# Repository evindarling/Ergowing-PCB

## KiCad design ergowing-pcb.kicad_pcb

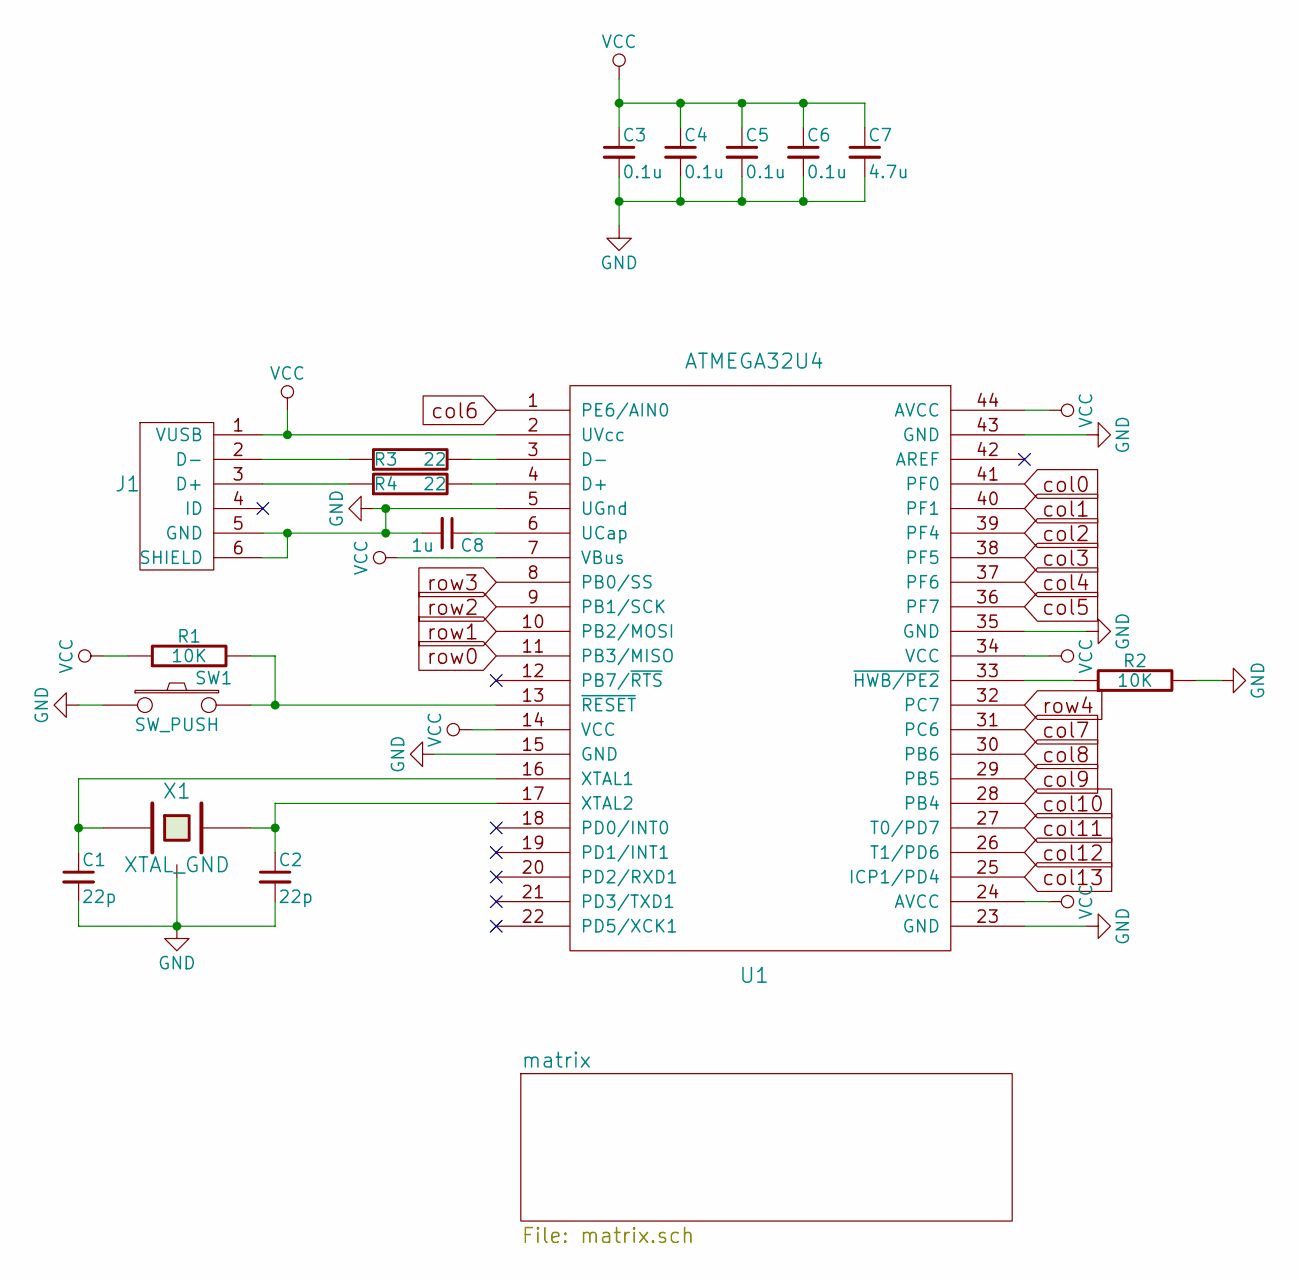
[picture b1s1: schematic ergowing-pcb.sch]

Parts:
C1, C2: 22p; C_0805_HandSoldering
C3, C4, C5, C6: 0.1u; C_0805_HandSoldering
C7: 4.7u; C_0805_HandSoldering
C8: 1u; C_0805_HandSoldering
J1: USB_mini_micro_B; USB_miniB_hirose_5S8
R1, R2: 10K; R_0805_HandSoldering
R3, R4: 22; R_0805_HandSoldering
SW1: SW_PUSH; SW_SPST_TL3342
U1: ATMEGA32U4; TQFP-44_10x10mm_Pitch0.8mm
X1: XTAL_GND; crystal_FA238-TSX3225

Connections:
GND: C1.2, C2.2, C3.2, C4.2, C5.2, C6.2, C7.2, C8.2, J1.5 (GND), J1.6 (SHIELD), R2.2, SW1.1, U1.5 (UGnd), U1.15 (GND), U1.23 (GND), U1.35 (GND), U1.43 (GND), X1.3; also elsewhere on the board
unnamed: C1.1, U1.16 (XTAL1), X1.1
unnamed: C2.1, U1.17 (XTAL2), X1.2
unnamed: C8.1, U1.6 (UCap)
unnamed: J1.2 (D-), R3.1
unnamed: J1.3 (D+), R4.1
unnamed: R1.2, SW1.2, U1.13 (~RESET)
unnamed: R2.1, U1.33 (~HWB/PE2)
unnamed: R3.2, U1.3 (D-)
unnamed: R4.2, U1.4 (D+)
VCC: C3.1, C4.1, C5.1, C6.1, C7.1, J1.1 (VUSB), R1.1, U1.2 (UVcc), U1.7 (VBus), U1.14 (VCC), U1.24 (AVCC), U1.34 (VCC), U1.44 (AVCC)
col0: U1.41 (PF0); also elsewhere on the board
col1: U1.40 (PF1); also elsewhere on the board
col2: U1.39 (PF4); also elsewhere on the board
col3: U1.38 (PF5); also elsewhere on the board
col4: U1.37 (PF6); also elsewhere on the board
col5: U1.36 (PF7); also elsewhere on the board
col6: U1.1 (PE6/AIN0); also elsewhere on the board
col7: U1.31 (PC6); also elsewhere on the board
col8: U1.30 (PB6); also elsewhere on the board
col9: U1.29 (PB5); also elsewhere on the board
col10: U1.28 (PB4); also elsewhere on the board
col11: U1.27 (T0/PD7); also elsewhere on the board
col12: U1.26 (T1/PD6); also elsewhere on the board
col13: U1.25 (ICP1/PD4); also elsewhere on the board
row0: U1.11 (PB3/MISO); also elsewhere on the board
row1: U1.10 (PB2/MOSI); also elsewhere on the board
row2: U1.9 (PB1/SCK); also elsewhere on the board
row3: U1.8 (PB0/SS); also elsewhere on the board
row4: U1.32 (PC7); also elsewhere on the board

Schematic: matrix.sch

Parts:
D0:0, D0:1, D0:2, D0:3, D0:4, D1:0, D1:1, D1:2, D1:3, D1:4, D2:0, D2:1, D2:2, D2:3, D2:4, D3:0, D3:1, D3:2, D3:3, D3:4, D4:0, D4:1, D4:2, D4:3, D4:4, D5:0, D5:1, D5:2, D5:3, D5:4, D6:0, D7:0, D7:4, D8:0, D8:1, D8:2, D8:3, D8:4, D9:0, D9:1, D9:2, D9:3, D9:4, D10:0, D10:1, D10:2, D10:3, D10:4, D11:0, D11:1, D11:2, D11:3, D11:4, D12:0, D12:1, D12:2, D12:3, D12:4, D13:0, D13:1, D13:2, D13:3, D13:4: D; D_SOD123_axial
D6:1, D6:3, D7:1, D7:3: D; Mx_Alps_150
K0:0, K0:1, K0:2, K0:3, K0:4: KEYSW; Mx_Alps_150_R-5deg
K1:0, K1:1, K1:2, K1:3, K1:4, K2:0, K2:1, K2:2, K2:3, K2:4, K3:0, K3:1, K3:2, K3:3, K3:4, K4:0, K4:1, K4:2, K4:3, K4:4, K5:0, K5:1, K5:2, K5:3, K6:0: KEYSW; Mx_Alps_100_R-5deg
K5:4: KEYSW; Mx_Alps_200
K6:1, K6:3, K7:1, K7:3: KEYSW; Mx_Alps_150
K7:0, K7:4, K8:0, K8:1, K8:2, K8:3, K8:4, K9:0, K9:1, K9:2, K9:3, K9:4, K10:0, K10:1, K10:2, K10:3, K10:4, K11:0, K11:1, K11:2, K11:3, K11:4, K12:0, K12:1, K12:2, K12:3, K12:4: KEYSW; Mx_Alps_100_R5deg
K13:0, K13:1, K13:2, K13:3, K13:4: KEYSW; Mx_Alps_150_R5deg

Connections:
unnamed: D0:0.2, K0:0.2
unnamed: D0:1.2, K0:1.2
unnamed: D0:2.2, K0:2.2
unnamed: D0:3.2, K0:3.2
unnamed: D0:4.2, K0:4.2
unnamed: D1:0.2, K1:0.2
unnamed: D1:1.2, K1:1.2
unnamed: D1:2.2, K1:2.2
unnamed: D1:3.2, K1:3.2
unnamed: D1:4.2, K1:4.2
unnamed: D2:0.2, K2:0.2
unnamed: D2:1.2, K2:1.2
unnamed: D2:2.2, K2:2.2
unnamed: D2:3.2, K2:3.2
unnamed: D2:4.2, K2:4.2
unnamed: D3:0.2, K3:0.2
unnamed: D3:1.2, K3:1.2
unnamed: D3:2.2, K3:2.2
unnamed: D3:3.2, K3:3.2
unnamed: D3:4.2, K3:4.2
unnamed: D4:0.2, K4:0.2
unnamed: D4:1.2, K4:1.2
unnamed: D4:2.2, K4:2.2
unnamed: D4:3.2, K4:3.2
unnamed: D4:4.2, K4:4.2
unnamed: D5:0.2, K5:0.2
unnamed: D5:1.2, K5:1.2
unnamed: D5:2.2, K5:2.2
unnamed: D5:3.2, K5:3.2
unnamed: D5:4.2, K5:4.2
unnamed: D6:0.2, K6:0.2
unnamed: D6:1.2, K6:1.2
unnamed: D6:3.2, K6:3.2
unnamed: D7:0.2, K7:0.2
unnamed: D7:1.2, K7:1.2
unnamed: D7:3.2, K7:3.2
unnamed: D7:4.2, K7:4.2
unnamed: D8:0.2, K8:0.2
unnamed: D8:1.2, K8:1.2
unnamed: D8:2.2, K8:2.2
unnamed: D8:3.2, K8:3.2
unnamed: D8:4.2, K8:4.2
unnamed: D9:0.2, K9:0.2
unnamed: D9:1.2, K9:1.2
unnamed: D9:2.2, K9:2.2
unnamed: D9:3.2, K9:3.2
unnamed: D9:4.2, K9:4.2
unnamed: D10:0.2, K10:0.2
unnamed: D10:1.2, K10:1.2
unnamed: D10:2.2, K10:2.2
unnamed: D10:3.2, K10:3.2
unnamed: D10:4.2, K10:4.2
unnamed: D11:0.2, K11:0.2
unnamed: D11:1.2, K11:1.2
unnamed: D11:2.2, K11:2.2
unnamed: D11:3.2, K11:3.2
unnamed: D11:4.2, K11:4.2
unnamed: D12:0.2, K12:0.2
unnamed: D12:1.2, K12:1.2
unnamed: D12:2.2, K12:2.2
unnamed: D12:3.2, K12:3.2
unnamed: D12:4.2, K12:4.2
unnamed: D13:0.2, K13:0.2
unnamed: D13:1.2, K13:1.2
unnamed: D13:2.2, K13:2.2
unnamed: D13:3.2, K13:3.2
unnamed: D13:4.2, K13:4.2
col0: K0:0.1, K0:1.1, K0:2.1, K0:3.1, K0:4.1; also elsewhere on the board
col1: K1:0.1, K1:1.1, K1:2.1, K1:3.1, K1:4.1; also elsewhere on the board
col2: K2:0.1, K2:1.1, K2:2.1, K2:3.1, K2:4.1; also elsewhere on the board
col3: K3:0.1, K3:1.1, K3:2.1, K3:3.1, K3:4.1; also elsewhere on the board
col4: K4:0.1, K4:1.1, K4:2.1, K4:3.1, K4:4.1; also elsewhere on the board
col5: K5:0.1, K5:1.1, K5:2.1, K5:3.1, K5:4.1; also elsewhere on the board
col6: K6:0.1, K6:1.1, K6:3.1; also elsewhere on the board
col7: K7:0.1, K7:1.1, K7:3.1, K7:4.1; also elsewhere on the board
col8: K8:0.1, K8:1.1, K8:2.1, K8:3.1, K8:4.1; also elsewhere on the board
col9: K9:0.1, K9:1.1, K9:2.1, K9:3.1, K9:4.1; also elsewhere on the board
col10: K10:0.1, K10:1.1, K10:2.1, K10:3.1, K10:4.1; also elsewhere on the board
col11: K11:0.1, K11:1.1, K11:2.1, K11:3.1, K11:4.1; also elsewhere on the board
col12: K12:0.1, K12:1.1, K12:2.1, K12:3.1, K12:4.1; also elsewhere on the board
col13: K13:0.1, K13:1.1, K13:2.1, K13:3.1, K13:4.1; also elsewhere on the board
row0: D0:0.1, D1:0.1, D2:0.1, D3:0.1, D4:0.1, D5:0.1, D6:0.1, D7:0.1, D8:0.1, D9:0.1, D10:0.1, D11:0.1, D12:0.1, D13:0.1; also elsewhere on the board
row1: D0:1.1, D1:1.1, D2:1.1, D3:1.1, D4:1.1, D5:1.1, D6:1.1, D7:1.1, D8:1.1, D9:1.1, D10:1.1, D11:1.1, D12:1.1, D13:1.1; also elsewhere on the board
row2: D0:2.1, D1:2.1, D2:2.1, D3:2.1, D4:2.1, D5:2.1, D8:2.1, D9:2.1, D10:2.1, D11:2.1, D12:2.1, D13:2.1; also elsewhere on the board
row3: D0:3.1, D1:3.1, D2:3.1, D3:3.1, D4:3.1, D5:3.1, D6:3.1, D7:3.1, D8:3.1, D9:3.1, D10:3.1, D11:3.1, D12:3.1, D13:3.1; also elsewhere on the board
row4: D0:4.1, D1:4.1, D2:4.1, D3:4.1, D4:4.1, D5:4.1, D7:4.1, D8:4.1, D9:4.1, D10:4.1, D11:4.1, D12:4.1, D13:4.1; also elsewhere on the board

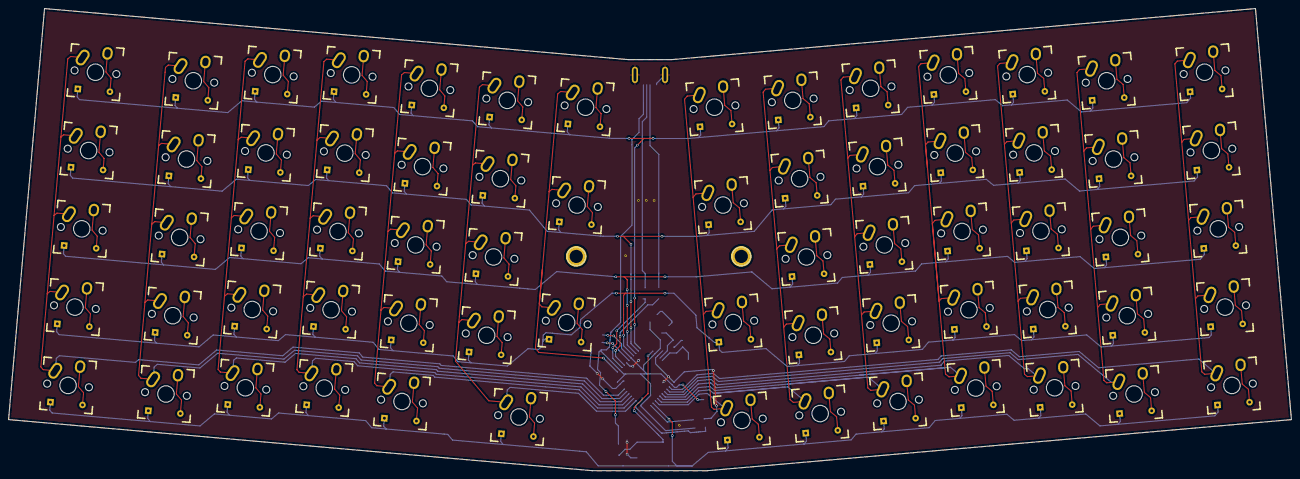
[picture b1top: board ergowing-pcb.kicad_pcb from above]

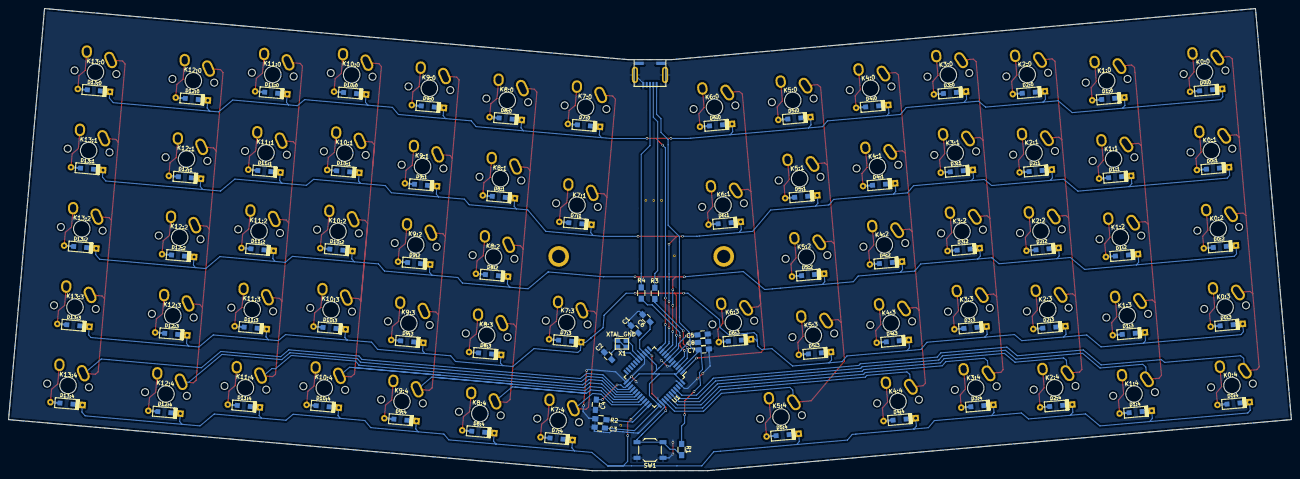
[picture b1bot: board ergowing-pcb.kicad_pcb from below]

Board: 2 copper layers, 310.9 x 112.0 mm, 157 parts (83 on the bottom side), 97 nets.

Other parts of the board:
mh1, mh2: 1pin
s2, s2#2, s2#3, s2#4, s2#5: VIA-0.6-f

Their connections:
GND: s2.1, s2#2.1, s2#3.1, s2#4.1, s2#5.1; also elsewhere on the board

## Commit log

2018-05-27 Switch matrix added, initial connections made
2018-05-27 Fix #1
2018-05-27 Associate components and footprints
2018-05-28 Organize footprints, create new 150 vertical footprint
2018-05-28 Temp #1
2018-05-28 Temp #2
2018-05-28 Revert "Temp #2"
    This reverts commit d15dc5ae93d42b7242c0dbe6693181fd858ed452.
2018-05-28 Revert "Temp #1"
    This reverts commit 8855f9af1857a61eabaf4ca8dbcabab4558a1e27.
2018-05-28 Key switches laid out
2018-05-28 Move keyswitch labels
2018-05-28 Place diodes
2018-05-28 Layout near completion
2018-05-28 Layout near completion #2
2018-05-28 Layout update, left and right are correct distance
2018-05-28 Update #321312
2018-05-28 Revert "Update #321312"
    This reverts commit 362bd967889284bfad0d96aa47e5c379ba675c40.
2018-05-28 Layout complete
2018-05-29 Revert "Layout complete"
    This reverts commit 59bf488b1ce8a9abcfbd41c5df7c21669f62f61c.
2018-05-29 Revert "Revert "Layout complete""
    This reverts commit 60232cbc4ae826425ac31cc95270d2e30684b4a9.
2018-05-29 Layout actually complete
2018-05-29 Fix misplaced key switches
2018-05-29 Left-hand side diodes placed
2018-05-29 Right-hand side diodes placed
2018-05-29 Pre-messing with schematic #1
2018-05-29 Place components
2018-05-29 Edge cut defined?
2018-05-30 Zones complete
2018-05-30 Pre-switch wiring
2018-05-30 Rows wired
2018-05-30 Connect switches to diodes
2018-05-30 Rows 0 & 1 wired
2018-05-30 Pre-messing around #1
2018-05-30 MCU row re-order
2018-05-31 Pre-row reorder #1
2018-05-31 Rows re-wired to be cleaner
2018-05-31 Progress #1
2018-06-01 Re-wire C5, C7, C8. Adjust row3
2018-06-02 Save point #1
2018-06-02 Save point #2
2018-06-02 ????2
2018-06-02 Revert "????2"
    This reverts commit e5e8950b7b1fdc3a4882abe6868fe531feca4c22.
2018-06-02 Revert "???"
    This reverts commit f7bf663342cbcfabebe868cd9da4599bfa985a74.
2018-06-02 Revert "Save point #2"
    This reverts commit fc0d8f0ac13c56613f6885e4d42e6bac5eee3c2f.
2018-06-02 Revert "Save point #1"
    This reverts commit 6e46eccd35bc3b538c0f31e6a4b9f04afbfbe96f.
2018-06-02 Revert "Re-wire C5, C7, C8. Adjust row3"
    This reverts commit 4ac69c9d6fc9758acc5c970c47322467544b3bea.
2018-06-02 Revert "Progress #1"
    This reverts commit 97b8e3d6074c7b26234465a4e1f34c47306f15ec.
2018-06-02 Revert "Rows re-wired to be cleaner"
    This reverts commit 00a00da537b04bf894fe4a5768944e963a032eb3.
2018-06-02 Revert "Pre-row reorder #1"
    This reverts commit 29f4975243a82b3ca362d304f8bba3963a4d9e5b.
2018-06-02 Revert "MCU row re-order"
    This reverts commit ad64f491a5b8dd37c3cc1eee55047beada38f830.
2018-06-02 Revert "Pre-messing around #1"
    This reverts commit 32e58cf0b1eda56b39c79379dba13b735693d8cf.
2018-06-02 Revert "Rows wired"
    This reverts commit d2347f7a43c37e1db01372e1be5a7f5dcf926aa7.
2018-06-02 Revert "Rows 0 & 1 wired"
    This reverts commit 709e624612da15180c7ef4b200a15a8fa3ce19e0.
2018-06-02 Revert "Rows wired"
    This reverts commit d70f662c53e392adef38fe5ef701a55c1d48fb42.
2018-06-02 Revert "Revert "Rows wired""
    This reverts commit e02774645a3a5369cedc409384393136fb4ce368.
2018-06-02 Revert "Connect switches to diodes"
    This reverts commit 2486d4e9eff35fc84fffcee9a461cbe5a4c6410b.
2018-06-02 Revert "Revert "Rows wired""
    This reverts commit adba6586d6cb1fc90ef0a2f50d1a669c9e1cd072.
2018-06-02 Revert "Revert "Connect switches to diodes""
    This reverts commit 033af0bf217f60402b18a45999197d4c36d7edb9.
2018-06-02 Revert "Revert "Revert "Rows wired"""
    This reverts commit ee1ec29523b9f231167a43a0f9d8c8bd97ae6fd3.
2018-06-02 Revert "Revert "Rows 0 & 1 wired""
    This reverts commit d8e63ab41f219ca85155c87a0aedad4b8828a49d.
2018-06-02 Revert "Revert "Rows wired""
    This reverts commit d8e93c14f2c4eb0c38e5446e086aed1a113cf798.
2018-06-02 Revert "Revert "Pre-messing around #1""
    This reverts commit bca496b8a638dc7197412f11c24a1b9ffcd84acd.
2018-06-02 Revert "Revert "MCU row re-order""
    This reverts commit 5d3f39a06eb83dde2531c95b88eab18761a104d1.
2018-06-02 Revert "Revert "Pre-row reorder #1""
    This reverts commit 4dfce21be10194d0f0da7844cb6ed8845da9265b.
2018-06-02 Revert "Revert "Rows re-wired to be cleaner""
    This reverts commit 08ffcdada99d0287513d1aed59b8cb3d44452ae5.
2018-06-02 Revert "Revert "Progress #1""
    This reverts commit 5a073aecdd5ac4e88074fab2064031910896d3f9.
2018-06-02 Revert "Revert "Re-wire C5, C7, C8. Adjust row3""
    This reverts commit c43a6ca9685387392931101dcc75c9cb56497815.
2018-06-02 Revert "Revert "Save point #1""
    This reverts commit 58ee8472bcfd6a6e4ae8dbf28a98d283358e8750.
2018-06-02 Revert "Revert "Save point #2""
    This reverts commit d41ea80a05a5be6f3e1bef164b82b24c2d6c7182.
2018-06-02 Revert "Revert "???""
    This reverts commit 5664838444f42f2c69b597d356240fce8c16d2d6.
2018-06-02 Revert "Revert "????2""
    This reverts commit 263d2973feb3adaa445a767927660b78f914ae6f.
2018-06-02 Fresh canvas
2018-06-02 Some rows
2018-06-03 Wiring progess
2018-06-03 Column progress
2018-06-04 Cols done
2018-06-04 Cols wired to MC
2018-06-04 More cols wired
2018-06-04 Cols finished
2018-06-04 Everything wired up. Looking into zones
2018-06-05 Modify schematics
2018-06-05 Add via stitching to fill in missing ground planes
2018-06-05 Minor modifications
2018-06-05 Correct edge cuts
2018-06-05 Add *-bak to .gitignore
2018-06-05 Remove -bak file
2018-06-05 Test
2018-06-07 Remove vias from USB tracks
2018-06-07 Remove K5:4's stabiliser holes
2018-06-07 Left side cols/rows retraced
2018-06-07 Right side cols/rows retraced
2018-06-07 Re-tracing complete. T-junctions replaced
2018-06-11 Begin redrawing the edge cuts
2018-06-11 Edge cuts lined up
2018-06-11 Update#1
2018-06-15 Start re-aligning keyswitches
2018-06-15 Col0 re-aligned
2018-06-15 Revert "w/e"
    This reverts commit 748dd809b2e3bdd7314f0de60f458a360d24b297.
2018-06-15 Revert "Col0 re-aligned"
    This reverts commit d7062fc702a203e387eedc3f1abee4cec9620dca.
2018-06-15 Col0 re-aligned *properly
2018-06-15 Col1 re-aligned
2018-06-15 Col2 re-aligned
2018-06-15 Col3 re-aligned
2018-06-15 Col4 re-aligned
2018-06-15 K5:4 re-aligned
2018-06-15 Col5 re-aligned
2018-06-15 Col6 re-aligned
2018-06-15 All cols re-aligned
2018-06-15 Edge cuts drawn & aligned perfectly
2018-06-15 Prep for cutout holes / GND zones
2018-06-23 Left-hand side col wires redone
2018-06-23 Right-hand side col wires redone
2018-06-24 Row wires redone
2018-06-24 Row fix #1
2018-06-24 Zones added
2018-06-24 Via stitches added
2018-06-24 Run DRC and correct all errors
2018-06-27 Add mounting holes
